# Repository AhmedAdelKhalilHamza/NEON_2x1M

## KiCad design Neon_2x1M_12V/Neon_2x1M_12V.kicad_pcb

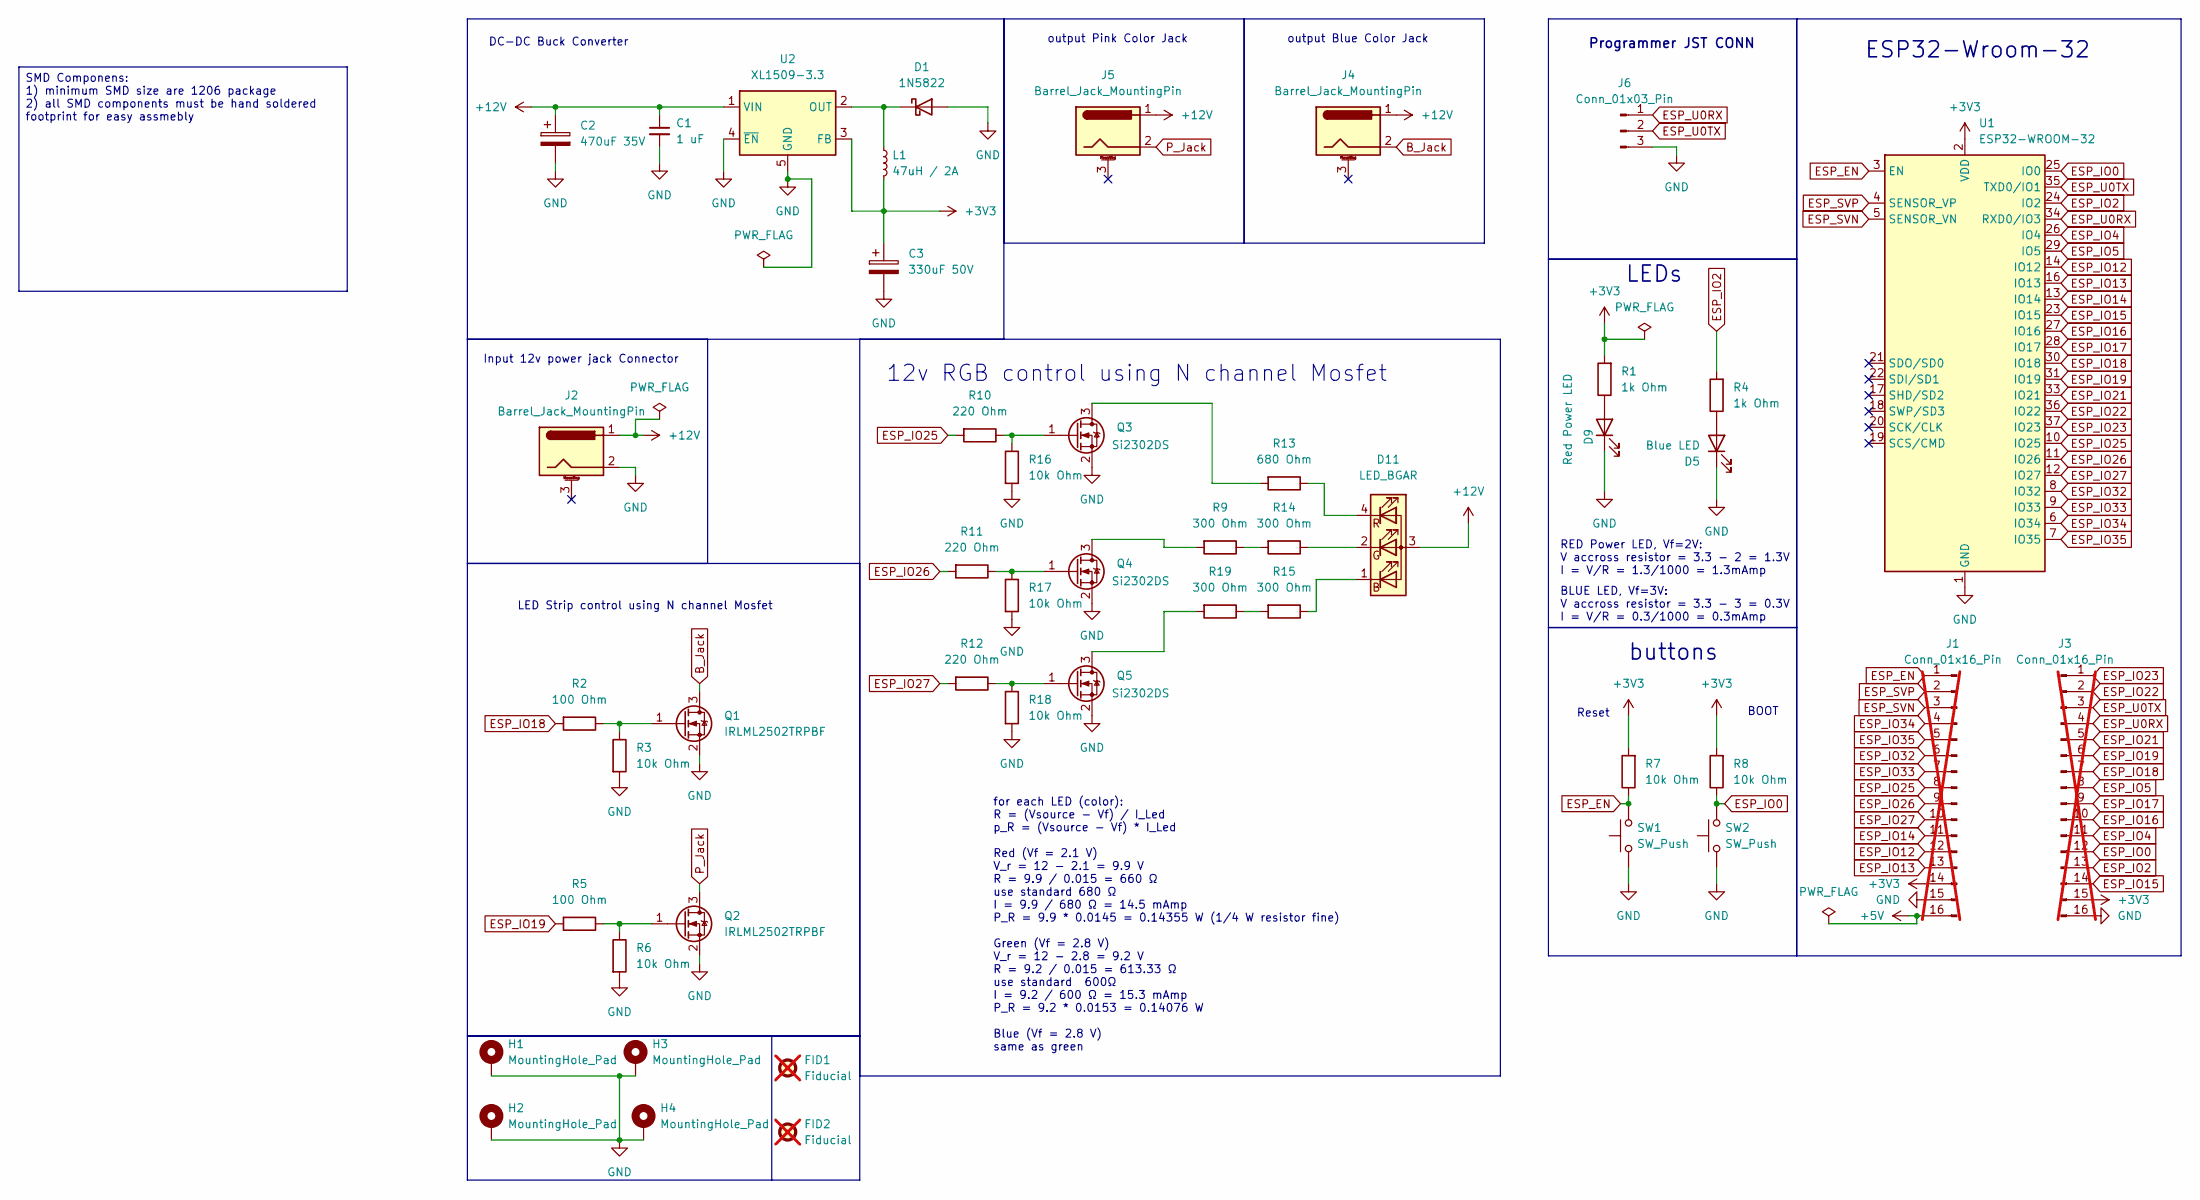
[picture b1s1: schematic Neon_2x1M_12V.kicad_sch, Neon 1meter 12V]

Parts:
C1: 1 uF; C_1206_3216Metric
C2: 470uF 35V; CP_Radial_D10.0mm_P5.00mm
C3: 330uF 50V; CP_Elec_10x10.5
D1: 1N5822; D_SMA
D5: Blue LED; LED_1206_3216Metric_Pad1.42x1.75mm_HandSolder
D9: Red Power LED; LED_1206_3216Metric_Pad1.42x1.75mm_HandSolder
D11: LED_BGAR; LED_D5.0mm-4_RGB
FID1, FID2: Fiducial; Fiducial_0.5mm_Mask1.5mm; not fitted
H1, H2, H3, H4: MountingHole_Pad; MountingHole_3.2mm_M3_Pad_Via
J1, J3: Conn_01x16_Pin; PinHeader_1x16_P2.54mm_Vertical; not fitted
J2, J4, J5: Barrel_Jack_MountingPin; BarrelJack_Horizontal
J6: Conn_01x03_Pin; PinHeader_1x03_P2.54mm_Vertical
L1: 47uH / 2A; CD43
Q1, Q2: IRLML2502TRPBF; custom_SOT23
Q3: Si2302DS; custom_SOT23
Q4, Q5: Si2302DS; SOT-23
R1, R4: 1k Ohm; R_1206_3216Metric_Pad1.30x1.75mm_HandSolder
R2, R5: 100 Ohm; R_1206_3216Metric_Pad1.30x1.75mm_HandSolder
R3, R6, R7, R8, R16, R17, R18: 10k Ohm; R_0805_2012Metric_Pad1.20x1.40mm_HandSolder
R9, R14, R15, R19: 300 Ohm; R_1206_3216Metric_Pad1.30x1.75mm_HandSolder
R10, R11, R12: 220 Ohm; R_1206_3216Metric_Pad1.30x1.75mm_HandSolder
R13: 680 Ohm; R_1206_3216Metric_Pad1.30x1.75mm_HandSolder
SW1, SW2: SW_Push; TS_button_3_4_2
U1: ESP32-WROOM-32
U2: XL1509-3.3; SOIC-8_3.9x4.9mm_P1.27mm

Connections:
+3V3: C3.1, J1.14, J3.15, L1.2, R1.2, R7.2, R8.2, U1.2 (VDD), U2.3 (FB)
+12V: C1.1, C2.1, D11.3 (A), J2.1, J4.1, J5.1, U2.1 (VIN)
B_Jack: J4.2, Q1.3 (D)
ESP_EN: J1.1, R7.1, SW1.2, U1.3 (EN)
ESP_IO0: J3.12, R8.1, SW2.2, U1.25 (IO0)
ESP_IO2: J3.13, R4.2, U1.24 (IO2)
ESP_IO4: J3.11, U1.26 (IO4)
ESP_IO5: J3.8, U1.29 (IO5)
ESP_IO12: J1.12, U1.14 (IO12)
ESP_IO13: J1.13, U1.16 (IO13)
ESP_IO14: J1.11, U1.13 (IO14)
ESP_IO15: J3.14, U1.23 (IO15)
ESP_IO16: J3.10, U1.27 (IO16)
ESP_IO17: J3.9, U1.28 (IO17)
ESP_IO18: J3.7, R2.2, U1.30 (IO18)
ESP_IO19: J3.6, R5.2, U1.31 (IO19)
ESP_IO21: J3.5, U1.33 (IO21)
ESP_IO22: J3.2, U1.36 (IO22)
ESP_IO23: J3.1, U1.37 (IO23)
ESP_IO25: J1.8, R10.2, U1.10 (IO25)
ESP_IO26: J1.9, R11.2, U1.11 (IO26)
ESP_IO27: J1.10, R12.2, U1.12 (IO27)
ESP_IO32: J1.6, U1.8 (IO32)
ESP_IO33: J1.7, U1.9 (IO33)
ESP_IO34: J1.4, U1.6 (IO34)
ESP_IO35: J1.5, U1.7 (IO35)
ESP_SVN: J1.3, U1.5 (SENSOR_VN)
ESP_SVP: J1.2, U1.4 (SENSOR_VP)
ESP_U0RX: J3.4, J6.1, U1.34 (RXD0/IO3)
ESP_U0TX: J3.3, J6.2, U1.35 (TXD0/IO1)
GND: C1.2, C2.2, C3.2, D1.2 (A), D5.1 (K), D9.1 (K), H1.1, H2.1, H3.1, H4.1, J1.15, J2.2, J3.16, J6.3, Q1.2 (S), Q2.2 (S), Q3.2 (S), Q4.2 (S), Q5.2 (S), R3.2, R6.2, R16.2, R17.2, R18.2, SW1.1, SW2.1, U1.1 (GND), U1.15 (GND), U1.38 (GND), U1.39 (GND), U2.4 (~EN), U2.5 (GND), U2.6 (GND), U2.7 (GND), U2.8 (GND)
unnamed: D1.1 (K), L1.1, U2.2 (OUT)
unnamed: D5.2 (A), R4.1
unnamed: D9.2 (A), R1.1
unnamed: D11.1 (BK), R15.1
unnamed: D11.2 (GK), R14.1
unnamed: D11.4 (RK), R13.1
unnamed: Q1.1 (G), R2.1, R3.1
unnamed: Q2.1 (G), R5.1, R6.1
unnamed: Q3.3 (D), R13.2
unnamed: Q3.1 (G), R10.1, R16.1
unnamed: Q4.3 (D), R9.2
unnamed: Q4.1 (G), R11.1, R17.1
unnamed: Q5.3 (D), R19.2
unnamed: Q5.1 (G), R12.1, R18.1
unnamed: R9.1, R14.2
unnamed: R15.2, R19.1
P_Jack: J5.2, Q2.3 (D)

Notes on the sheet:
ESP32-Wroom-32
LED Strip control using N channel Mosfet
DC-DC Buck Converter
buttons
output Pink Color Jack
RED Power LED, Vf=2V: V accross resistor = 3.3 - 2 = 1.3V I = V/R = 1.3/1000 = 1.3mAmp
Input 12v power jack Connector
for each LED (color): R = (Vsource - Vf) / I_Led p_R = (Vsource - Vf) * I_Led Red (Vf = 2.1 V) V_r = 12 − 2.1 = 9.9 V R = 9.9 / 0.015 = 660 Ω use standard 680 Ω I = 9.9 / 680 Ω = 14.5 mAmp P_R = 9.9 * 0.0145 = 0.14355 W (1/4 W resistor fine) Green (Vf = 2.8 V) V_r = 12 − 2.8 = 9.2 V R = 9.2 / 0.015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
12v RGB control using N channel Mosfet
Reset
BLUE LED, Vf=3V: V accross resistor = 3.3 - 3 = 0.3V I = V/R = 0.3/1000 = 0.3mAmp
LEDs
BOOT
output Blue Color Jack
Programmer JST CONN
SMD Componens: 1) minimum SMD size are 1206 package 2) all SMD components must be hand soldered footprint for easy assmebly

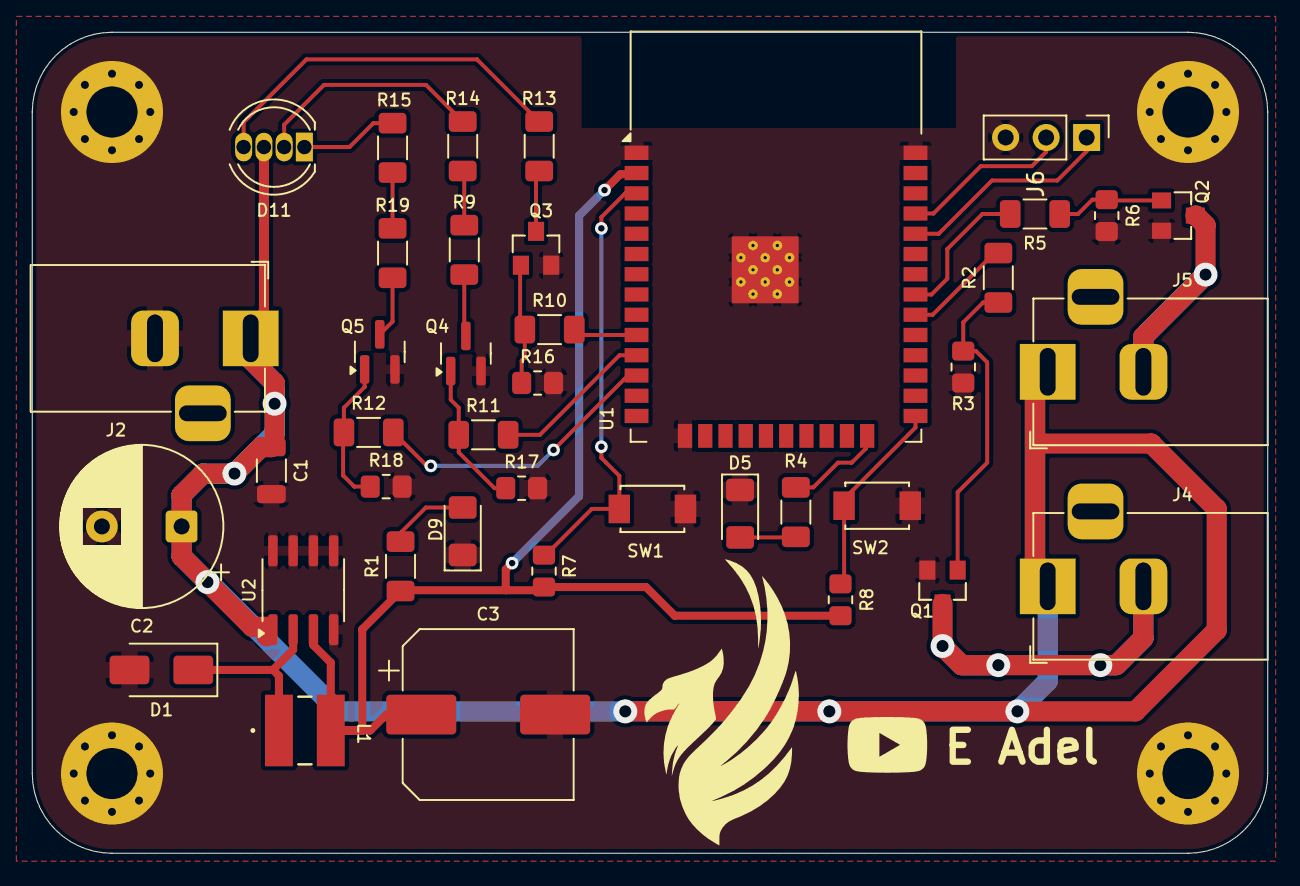
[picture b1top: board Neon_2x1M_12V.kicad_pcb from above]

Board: 2 copper layers, 77.5 x 51.5 mm, 44 parts (0 on the bottom side), 31 nets.

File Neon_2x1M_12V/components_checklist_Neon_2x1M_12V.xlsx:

Reference | Qty | Value | DNP | Exclude from BOM | Exclude from Board | Footprint | purchased components | link
C1 | 1 | 1 uF |  |  |  | Capacitor_SMD:C_1206_3216Metric | done | https://uge-one.com/product/smd-chip-capacitor-size-1206-1uf/
C2 | 1 | 470uF 35V |  |  |  | Capacitor_THT:CP_Radial_D10.0mm_P5.00mm |  | https://makerselectronics.com/product/capacitor-470uf-35v-10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
C3 | 1 | 330uF 50V |  |  |  | Capacitor_SMD:CP_Elec_10x10.5 | done | https://uge-one.com/product/smd-aluminum-electrolytic-capaci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
D1 | 1 | 1N5822 |  |  |  | Diode_SMD:D_SMA | done | https://uge-one.com/product/smd-schottky-diode-3a-40v-1n5822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
D5 | 1 | Blue LED |  |  |  | LED_SMD:LED_1206_3216Metric_Pad1.42x1.75mm_HandSolder | done | https://makerselectronics.com/product/smd-led-blue-1206/
D9 | 1 | Red Power LED |  |  |  | LED_SMD:LED_1206_3216Metric_Pad1.42x1.75mm_HandSolder | done | https://makerselectronics.com/product/smd-led-red-1206/
D11 | 1 | LED_BGAR |  |  |  | LED_THT:LED_D5.0mm-4_RGB | done | https://makerselectronics.com/product/rgb-diffused-led-commo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
J2,J4,J5 | 3 | Barrel_Jack_MountingPin |  |  |  | Connector_BarrelJack:BarrelJack_Horizontal | done
J6 | 1 | Conn_01x03_Pin |  |  |  | Connector_PinHeader_2.54mm:PinHeader_1x03_P2.54mm_Vertical | done | https://microohm-eg.com/product/jst-3-pin-90-degree-male-connector/
L1 | 1 | 47uH / 2A |  |  |  | CD43_Inductor:CD43 | done | https://uge-one.com/product/smd-power-inductor-470uh-4-5x4x3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
Q1,Q2 | 2 | IRLML2502TRPBF |  |  |  | custom_SOT23:custom_SOT23 |  | https://uge-one.com/product/smd-irlml2502trpbf-sot-23-mosfet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
Q3 | 1 | BSS138 |  |  |  | custom_SOT23:custom_SOT23 |  | https://makerselectronics.com/product/smd-mosfet-transistor-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
Q4,Q5 | 2 | BSS138 |  |  |  | Package_TO_SOT_SMD:SOT-23 |  | https://makerselectronics.com/product/smd-mosfet-transistor-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
R1 | 1 | 2.2k Ohm |  |  |  | Resistor_SMD:R_1206_3216Metric_Pad1.30x1.75mm_HandSolder |  | https://makerselectronics.com/product/chip-resistor-smd-2-2k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
R2,R5 | 2 | 100 Ohm |  |  |  | Resistor_SMD:R_1206_3216Metric_Pad1.30x1.75mm_HandSolder |  | https://uge-one.com/product/smd-chip-resistor-size-1206-100r-ohm/
R3,R6,R7,R8,R16,R17,R18 | 7 | 10k Ohm |  |  |  | Resistor_SMD:R_0805_2012Metric_Pad1.20x1.40mm_HandSolder | done | https://uge-one.com/product/0805-smd-chip-resistor-10k/?srsl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
R4 | 1 | 1k Ohm |  |  |  | Resistor_SMD:R_1206_3216Metric_Pad1.30x1.75mm_HandSolder |  | https://makerselectronics.com/product/chip-resistor-smd-1k%c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
R9,R14,R15,R19 | 4 | 300 Ohm |  |  |  | Resistor_SMD:R_1206_3216Metric_Pad1.30x1.75mm_HandSolder |  | https://uge-one.com/product/smd-chip-resistor-size-1206-300r-ohm/
R10,R11,R12 | 3 | 220 Ohm |  |  |  | Resistor_SMD:R_1206_3216Metric_Pad1.30x1.75mm_HandSolder |  | https://uge-one.com/product/smd-chip-resistor-size-1206-220r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
R13 | 1 | 660 Ohm |  |  |  | Resistor_SMD:R_1206_3216Metric_Pad1.30x1.75mm_HandSolder |  | https://makerselectronics.com/product/chip-resistor-smd-680%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
SW1,SW2 | 2 | SW_Push |  |  |  | TS_button_3_4_2:TS_button_3_4_2 | done | https://uge-one.com/product/smd-micro-push-button-switch-2p-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
U1 | 1 | ESP32-WROOM-32 |  |  |  | RF_Module:ESP32-WROOM-32 | done | https://uge-one.com/product/espressif-esp32-wroom-32-dual-co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
U2 | 1 | XL1509-3.3 |  |  |  | Package_SO:SOIC-8_3.9x4.9mm_P1.27mm | done | https://uge-one.com/product/xl1509-3-3e1-2a-150khz-buck-dc-d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

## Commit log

2025-10-31 added dc-dc buck converter to schematic
2025-11-02 updated schematic
2025-11-02 added external JST programmer connector
2025-11-03 updated BOM
2025-11-04 updated component placement
2025-11-04 updated 1x3 pin header jst connector footprint
2025-11-06 updated placement removed pinheaders
2025-11-06 updated logos and added pharohs logo
2025-11-06 update mounting holes placement
2025-11-06 fast routing
2025-11-06 updated tutankhamon logo
2025-11-06 updated routing and tutankhamon place on b.silkscreen
2025-11-07 chnaged some of sot23 to be custom footprint to see which is better in hand soldering
2025-11-08 Rename project from NEON_5M to NEON_2x1M
2025-11-08 updated output jack routing
2025-11-08 updated JST PIN header placement
2025-11-08 fixed some vias diameters
2025-11-08 updatd components checklist
2025-11-08 update BOM only 1k resistor is needed
2025-11-09 removed blue led and replaced it with red one and also updated their current imiting resistor
